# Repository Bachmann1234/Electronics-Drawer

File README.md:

# Electronics Drawer

Repo to collect source code and other artifacts around small electronics projects

## Cocktail Scale

A custom kitchen scale designed for use in a bar to measure cocktail ingrediants

## Giant Button

Giant Keyboard switch that can be programmed to do various keyboard tricks

## Eink Art Display

Eink displayed powered by a pi that displays art from the internet

## Sit Stand Timer

Two timers that track if my standing desk is up or down using a sonar sensor

## USB Morse Code Key

USB Morse Code Key that can be used as an external keyboard for an android phone

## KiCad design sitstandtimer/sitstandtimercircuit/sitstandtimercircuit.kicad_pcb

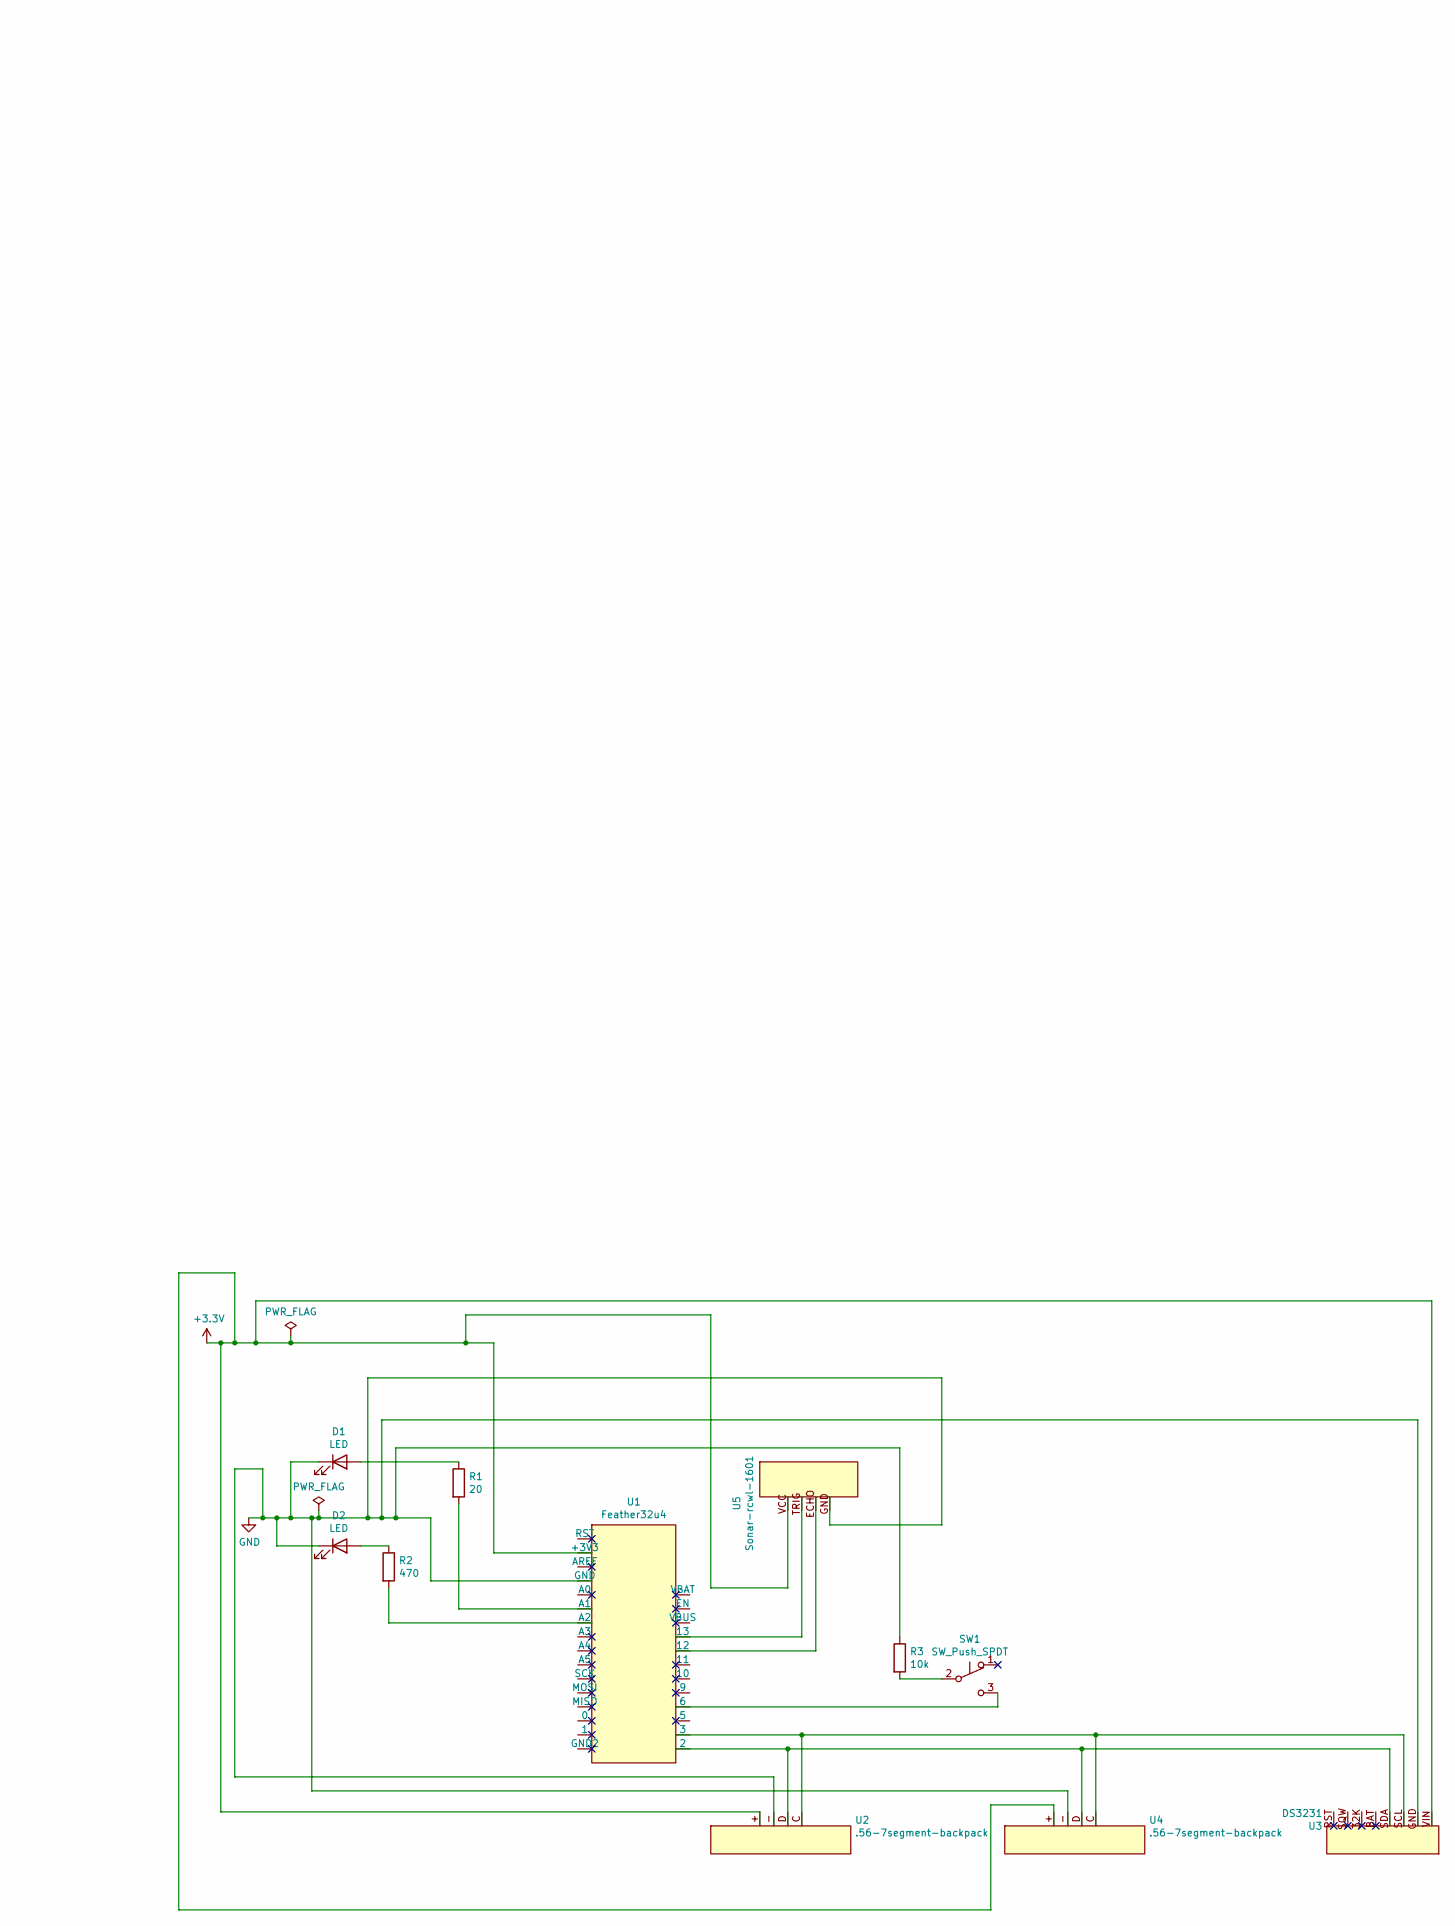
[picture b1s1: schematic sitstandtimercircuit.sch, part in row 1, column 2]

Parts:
D1, D2: LED; LED_D5.0mm
R1: 20; R_Axial_DIN0207_L6.3mm_D2.5mm_P10.16mm_Horizontal
R2: 470; R_Axial_DIN0207_L6.3mm_D2.5mm_P10.16mm_Horizontal
R3: 10k; R_Axial_DIN0207_L6.3mm_D2.5mm_P10.16mm_Horizontal
SW1: SW_Push_SPDT; button
U1: Feather32u4; Feather
U2, U4: .56-7segment-backpack; 7segmentbackpack
U3: DS3231; RTC
U5: Sonar-rcwl-1601; sonar

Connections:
+3V3: U1.+3V3, U2.+, U3.VIN, U4.+, U5.VCC
GND: D1.1 (K), D2.1 (K), R3.1, U1.GND, U2.-, U3.GND, U4.-, U5.GND
unnamed: D1.2 (A), R1.1
unnamed: D2.2 (A), R2.1
unnamed: R1.2, U1.A1
unnamed: R2.2, U1.A2
unnamed: R3.2, SW1.2 (B)
unnamed: SW1.3 (C), U1.6
unnamed: U1.2, U2.D, U3.SDA, U4.D
unnamed: U1.3, U2.C, U3.SCL, U4.C
unnamed: U1.12, U5.ECHO
unnamed: U1.13, U5.TRIG

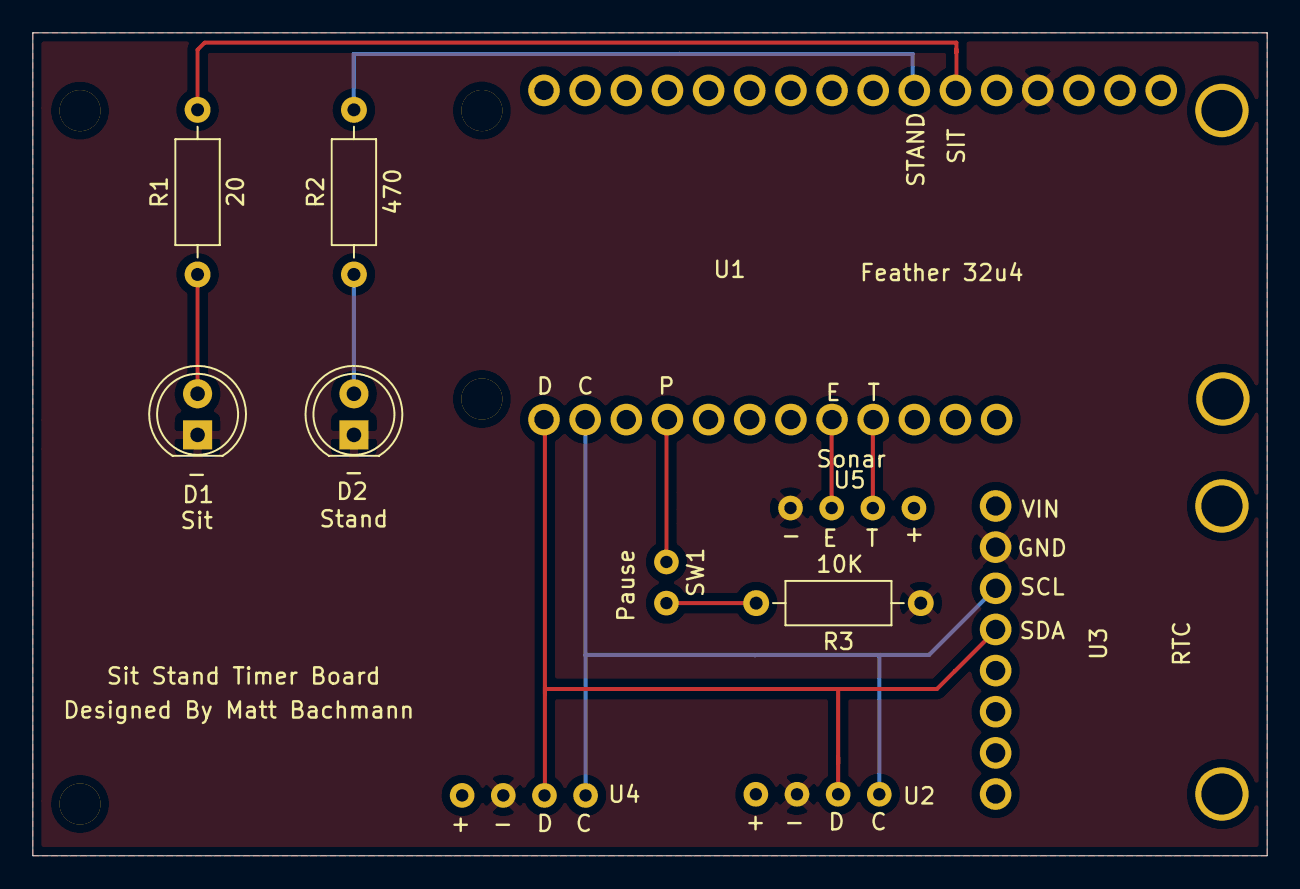
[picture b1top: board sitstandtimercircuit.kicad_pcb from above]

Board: 2 copper layers, 76.2 x 50.8 mm, 11 parts (0 on the bottom side), 12 nets.

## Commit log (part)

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2021-01-31 add a gitignore
2021-01-31 Add readme
2021-02-03 Inital scale prototype
2021-02-04 Round to the nearest gram. Convert to fluid ounces
    Dynamic font size based on value
2021-02-04 Update scale.ino
    calibration for nano
2021-02-04 Update scale.ino
    more tweaks to calibration
2021-02-04 Update scale.ino
    More calibration
2021-02-04 show two decimal points
2021-02-04 use oz instead of fluid oz
2021-02-04 font too big for 4 digits
2021-02-04 calibrate tweak
2021-02-04 Tare on start
2021-02-05 nested dirs do nothing
2021-02-05 Add keyboard code
2021-02-07 Add some pictures
2021-02-07 Add some photos and more detail to the readme
2021-02-07 Got the metropolitan art api working
2021-02-07 Some tweaks. Turns out some data is not always there
2021-02-07 Add basic program sturcture
2021-02-07 Add deviantart src
2021-02-07 Add code for the eink project
2021-02-07 rename some images
2021-02-07 add image to main readme
2021-02-07 Remove resize
2021-02-07 Add all images to home
2021-02-07 Add some supporting files
2021-02-07 I dont want the clean and the art to collide
2021-02-07 Add reddit r/art as a source
2021-02-07 Adds the art source to the footer/output. Uses auto board rather than specifying a specific one
2021-02-19 Add code fot the sit stand timer
2021-02-19 Add comment exlaining why I did not use the blinkrate function
2021-02-19 remove commented out line
2021-02-19 Minor refactorings
2021-02-19 Fix for the readme
2021-02-19 add sitstandtimer to the readme
2021-02-19 Typo in readme
2021-02-19 When debuging introduce a delay so I can actually see output in the serial monitor
2021-02-21 Adjustments for new board and new design with sonar pointing DOWN
2021-02-23 Tweaks to support status LEDS and introduce a delay for better sonar reporting
2021-02-23 Working color version I wanna try and generalize to work for both
2021-02-23 Generalize the conversion and footer functions a hint
2021-02-23 Use auto rather than importing a specific inky
2021-02-23 Generalize this so it works on both the WHAT and the IMPRESSION
2021-02-23 The color display does not clean, but it does need to clear itself
2021-02-23 Clarify the clear function is just for color
2021-02-23 Add a url source which is useful for testing and comparing the two displays
2021-02-27 Change switch to a 2 pin switch connected to ground and pin
2021-02-28 Add cad files for the sit stand timer
2021-02-28 Swap in latest prototype
2021-03-13 board v2
    More mounting holes
    Larger holes for components mounted with breadboard headers
2022-03-26 Add morse keyboard
2022-09-13 Frame stls
2022-09-25 Change to work on feather and a smaller display
2022-09-25 adds low battery warning and other tweaks
2024-01-06 Rename this file so arduino ide opens it
2024-11-10 Update this url as the popular api no longer exists
